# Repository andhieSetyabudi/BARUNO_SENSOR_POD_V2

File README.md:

# BARUNO_SENSOR_POD_V2https://github.com/andhieSetyabudi/BARUNO_SENSOR_POD_V2
Baruno sensor pod revision

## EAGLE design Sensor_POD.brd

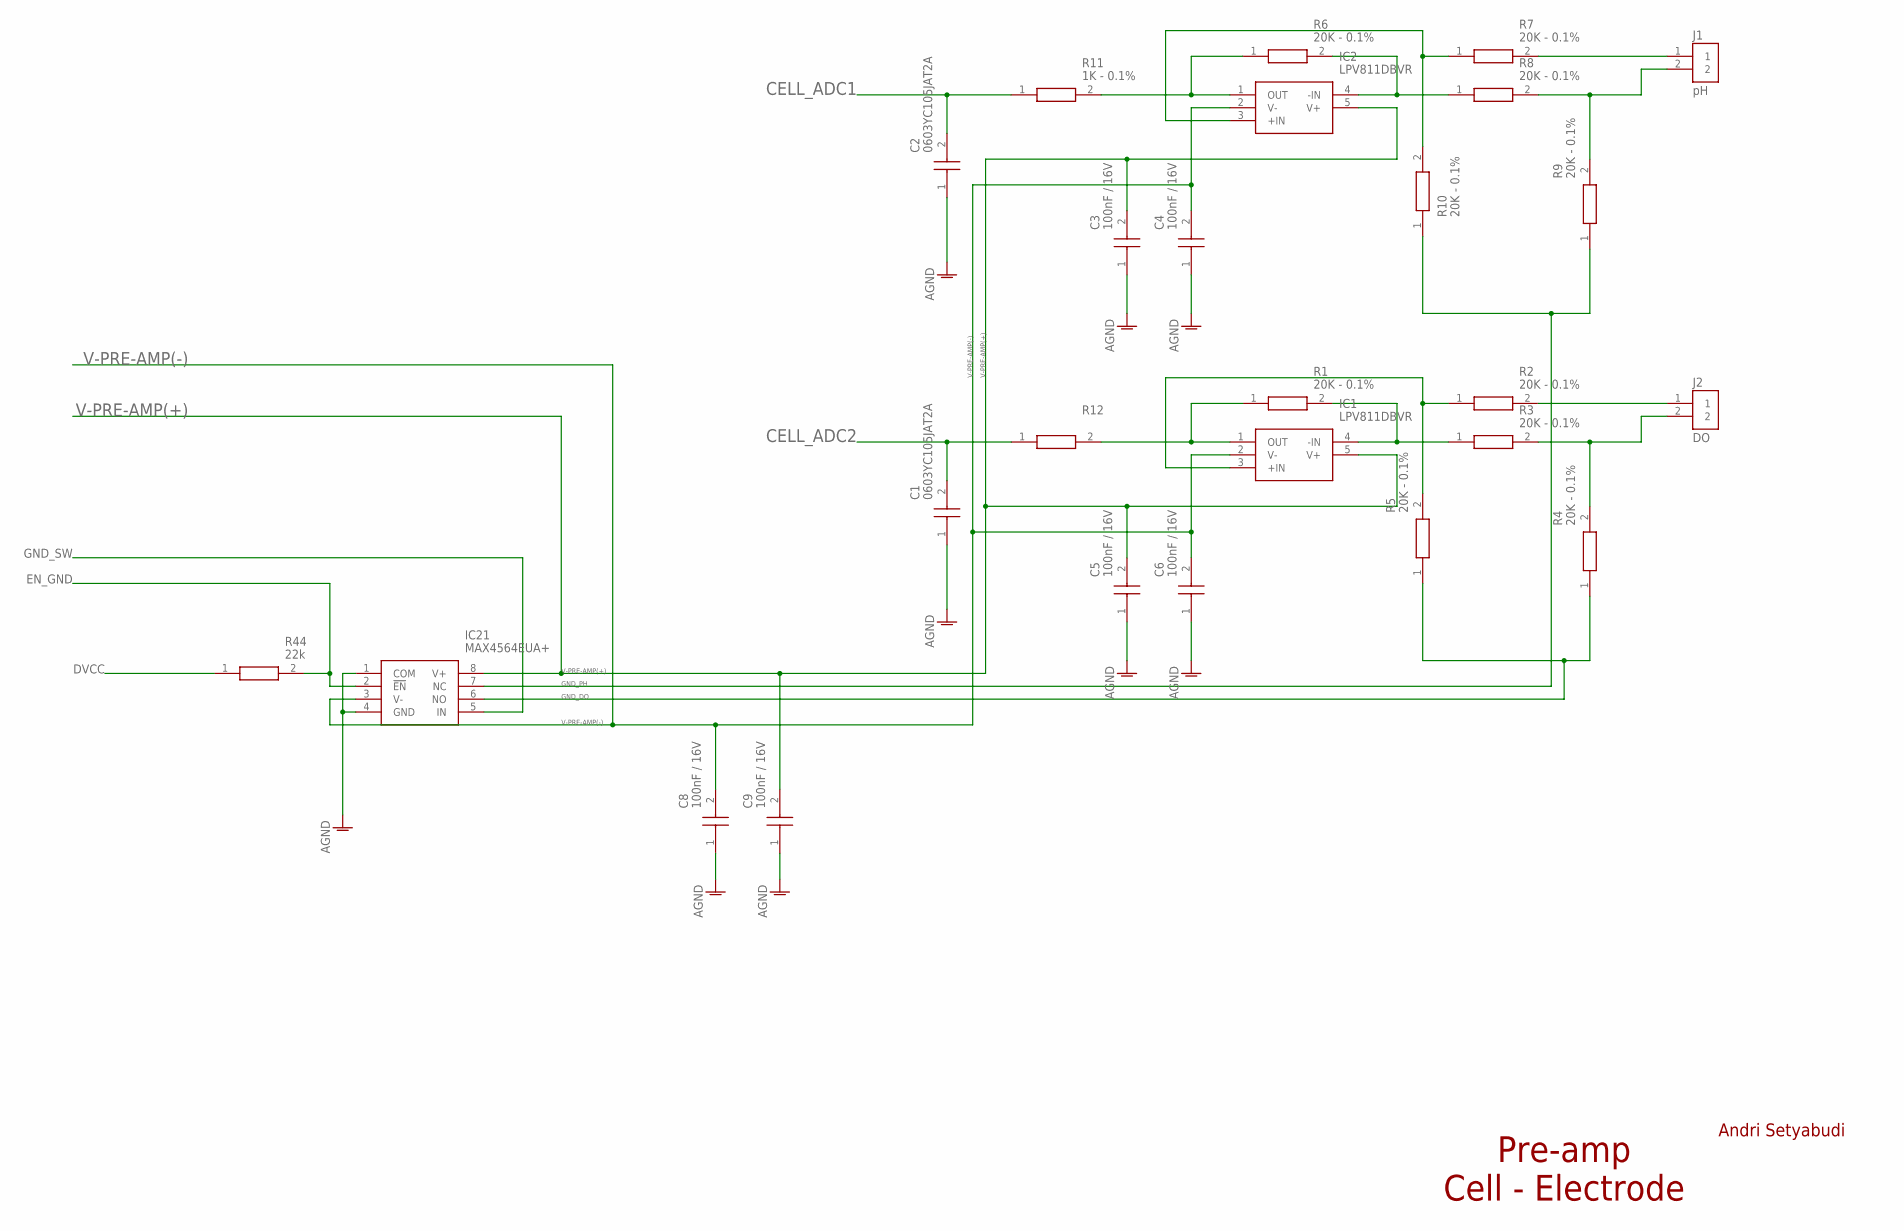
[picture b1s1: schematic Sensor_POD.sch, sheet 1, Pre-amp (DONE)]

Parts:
C1, C2: 0603YC105JAT2A; CAPC1608X90N
C3, C4, C5, C6, C8, C9: 100nF / 16V; CAPC1608X90N
IC1, IC2: LPV811DBVR; SOT95P280X145-5N
IC21: MAX4564EUA+; SOP65P490X110-8N
J1: pH; JST_B2B-PH-K-S(LF)(SN)
J2: DO; JST_B2B-PH-K-S(LF)(SN)
R1, R2, R3, R4, R5, R6, R7, R8, R9, R10: 20K - 0.1%; RESC1608X55N@2
R11: 1K - 0.1%; RESC1608X50N
R12: RG1608P-102-B-T5; RESC1608X50N
R44: 22k; RESC1608X55N

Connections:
AGND: C1.1, C2.1, C3.1, C4.1, C5.1, C6.1, C8.1, C9.1, IC21.1 (COM), IC21.4 (GND); also elsewhere on the board
CELL_ADC1: C2.2, R11.1; also elsewhere on the board
CELL_ADC2: C1.2, R12.1; also elsewhere on the board
DVCC: R44.1; also elsewhere on the board
EN_GND: IC21.2 (!EN), R44.2; also elsewhere on the board
GND_DO: IC21.6 (NO), R4.1, R5.1
GND_PH: IC21.7 (NC), R9.1, R10.1
GND_SW: IC21.5 (IN); also elsewhere on the board
unnamed: IC1.4 (-IN), R1.2, R3.1
unnamed: IC1.1 (OUT), R1.1, R12.2
unnamed: IC1.3 (+IN), R2.1, R5.2
unnamed: J2.2, R3.2, R4.2
unnamed: J2.1, R2.2
unnamed: IC2.4 (-IN), R6.2, R8.1
unnamed: IC2.1 (OUT), R6.1, R11.2
unnamed: IC2.3 (+IN), R7.1, R10.2
unnamed: J1.2, R8.2, R9.2
unnamed: J1.1, R7.2
V-PRE-AMP(+): C3.2, C5.2, C9.2, IC1.5 (V+), IC2.5 (V+), IC21.8 (V+); also elsewhere on the board
V-PRE-AMP(-): C4.2, C6.2, C8.2, IC1.2 (V-), IC2.2 (V-), IC21.3 (V-); also elsewhere on the board

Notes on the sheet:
Andri Setyabudi
Pre-amp Cell - Electrode

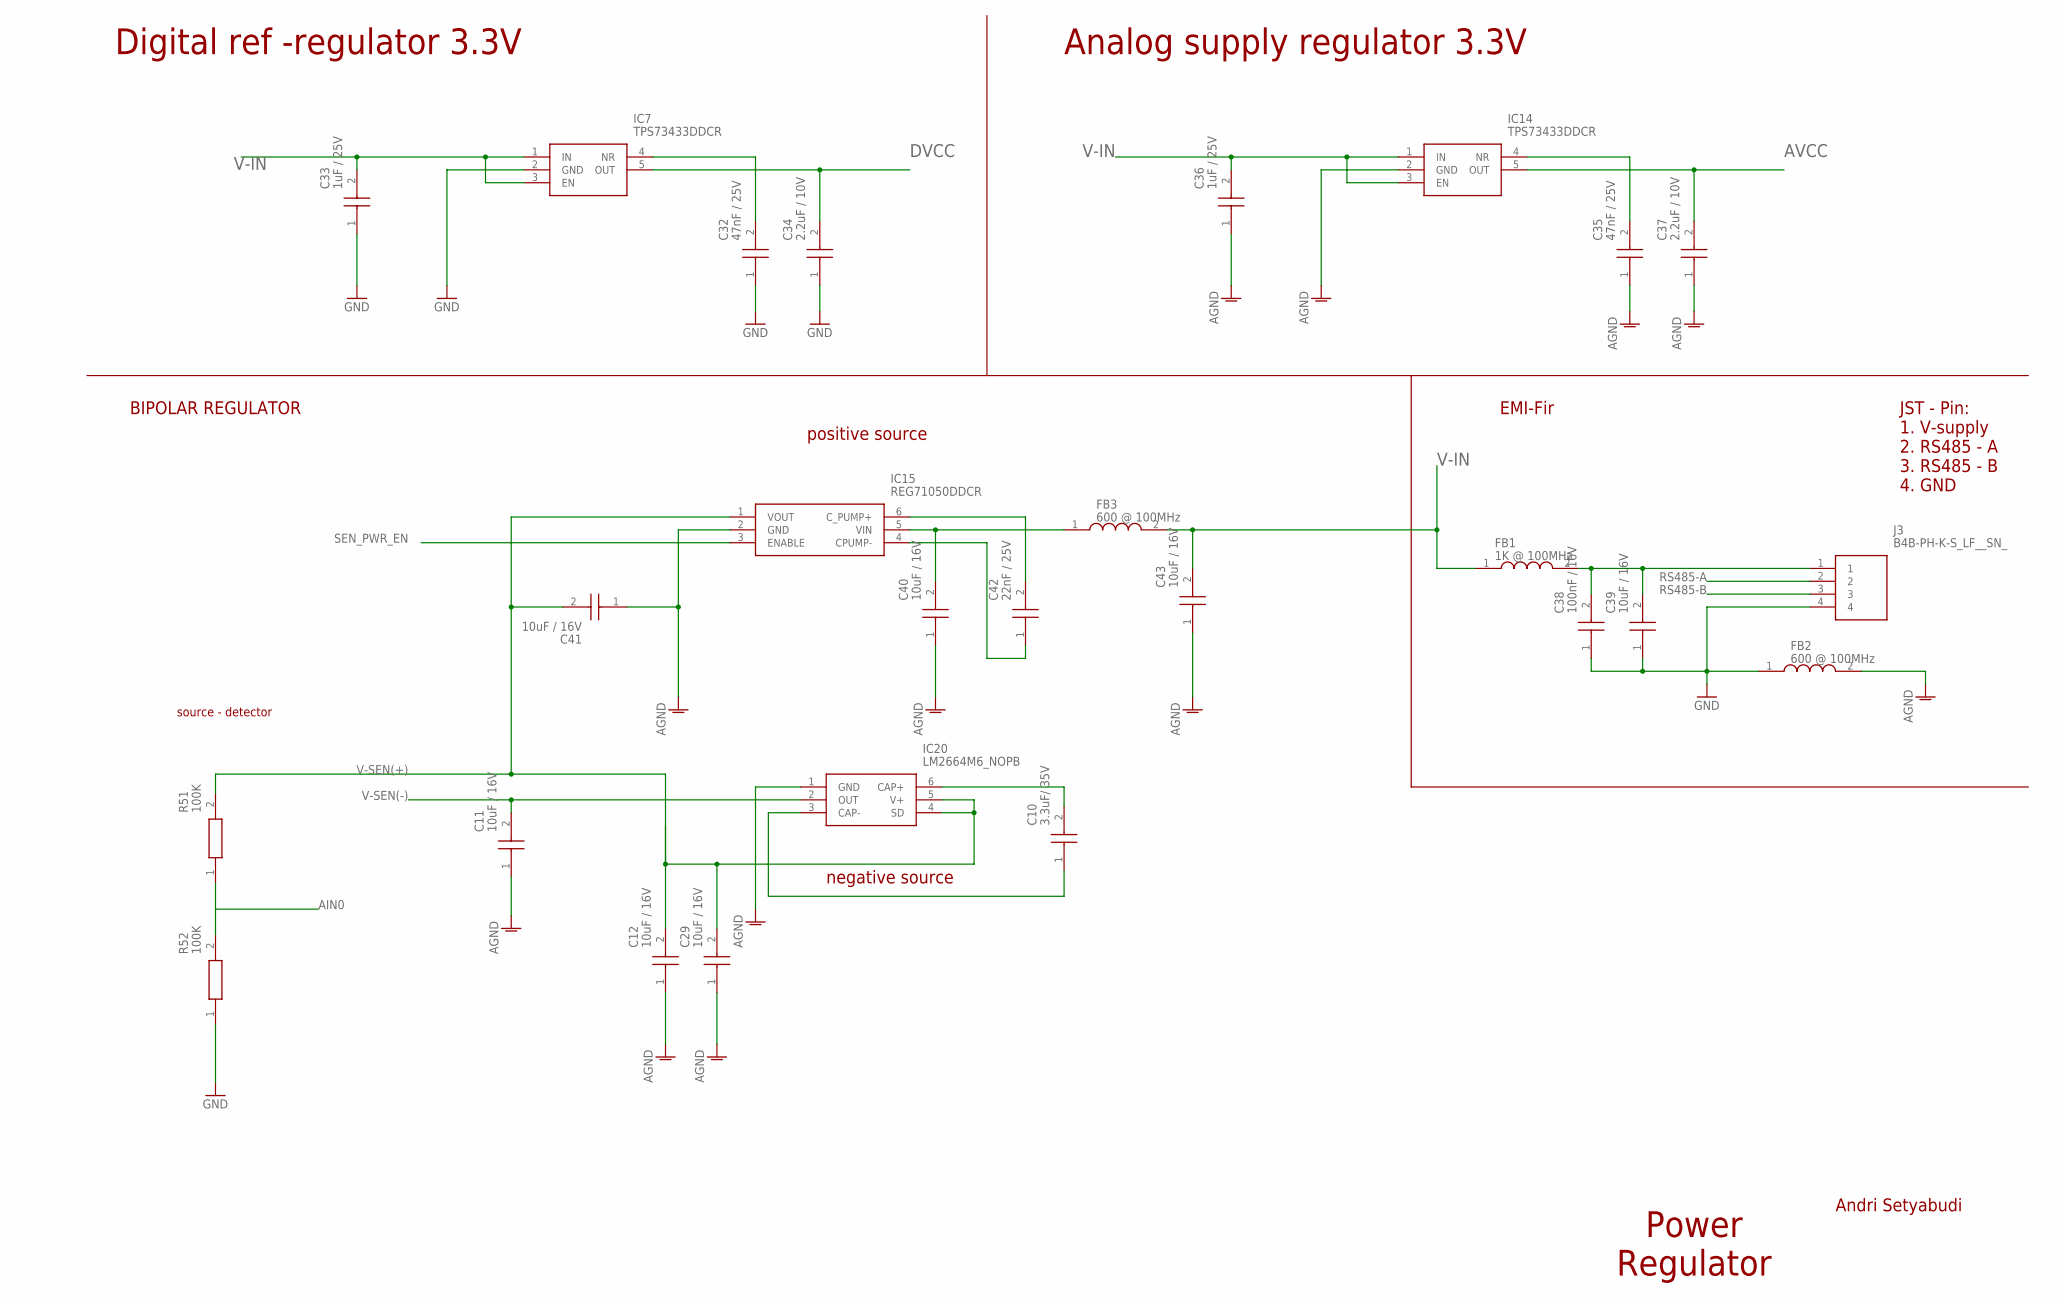
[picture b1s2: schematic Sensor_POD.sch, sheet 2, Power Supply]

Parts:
C10: 3.3uF/ 35V; CAPC1608X90N
C11, C12, C29, C39, C40, C41, C43: 10uF / 16V; CAPC1608X100N
C32, C35: 47nF / 25V; CAPC1608X90N@1
C33, C36: 1uF / 25V; CAPC1608X90N@1
C34, C37: 2.2uF / 10V; CAPC1608X90N@1
C38: 100nF / 16V; CAPC1608X90N@1
C42: 22nF / 25V; CAPC1608X90N@1
FB1: 1K @ 100MHz; BLM18KG102SH1J
FB2, FB3: 600 @ 100MHz; BEADC1608X75N
IC7, IC14: TPS73433DDCR; SOT95P280X110-5N
IC15: REG71050DDCR; SOT95P280X110-6N
IC20: LM2664M6_NOPB; SOT95P280X145-6N
J3: B4B-PH-K-S_LF__SN_; SHDR4W50P0X200_1X4_990X450X600
R51, R52: 100K; RESC1608X55N@1

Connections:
AGND: C11.1, C12.1, C29.1, C35.1, C36.1, C37.1, C40.1, C41.1, C43.1, FB2.2, IC14.2 (GND), IC15.2 (GND), IC20.1 (GND); also elsewhere on the board
AIN0: R51.1, R52.2; also elsewhere on the board
AVCC: C37.2, IC14.5 (OUT); also elsewhere on the board
DVCC: C34.2, IC7.5 (OUT); also elsewhere on the board
GND: C32.1, C33.1, C34.1, C38.1, C39.1, FB2.1, IC7.2 (GND), J3.4, R52.1; also elsewhere on the board
unnamed: C42.2, IC15.6 (C_PUMP+)
unnamed: C10.2, IC20.6 (CAP+)
unnamed: C42.1, IC15.4 (CPUMP-)
unnamed: C10.1, IC20.3 (CAP-)
unnamed: C32.2, IC7.4 (NR)
unnamed: C40.2, FB3.1, IC15.5 (VIN)
unnamed: C35.2, IC14.4 (NR)
unnamed: C38.2, C39.2, FB1.2, J3.1
RS485-A: J3.2; also elsewhere on the board
RS485-B: J3.3; also elsewhere on the board
SEN_PWR_EN: IC15.3 (ENABLE); also elsewhere on the board
V-IN: C33.2, C36.2, C43.2, FB1.1, FB3.2, IC7.1 (IN), IC7.3 (EN), IC14.1 (IN), IC14.3 (EN); also elsewhere on the board
V-SEN(+): C12.2, C29.2, C41.2, IC15.1 (VOUT), IC20.4 (SD), IC20.5 (V+), R51.2; also elsewhere on the board
V-SEN(-): C11.2, IC20.2 (OUT); also elsewhere on the board

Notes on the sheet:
Andri Setyabudi
Power Regulator
negative source
Digital ref -regulator 3.3V
Analog supply regulator 3.3V
BIPOLAR REGULATOR
EMI-Fir
JST - Pin: 1. V-supply 2. RS485 - A 3. RS485 - B 4. GND
positive source
source - detector

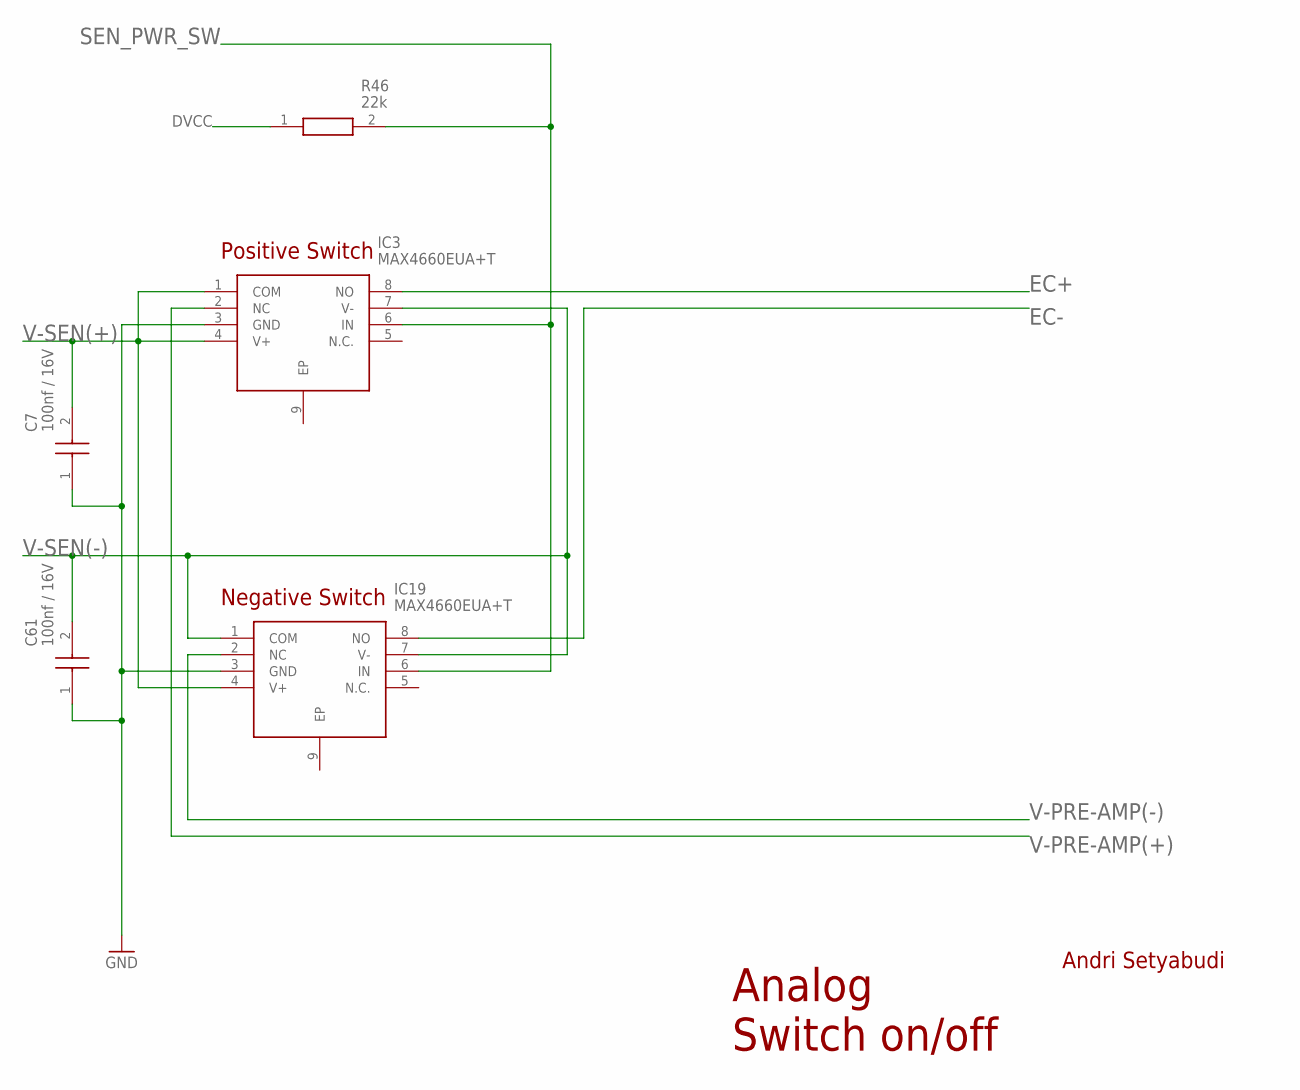
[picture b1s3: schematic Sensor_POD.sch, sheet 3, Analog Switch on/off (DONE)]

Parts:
C7, C61: 100nf / 16V; CAPC1608X90N
IC3, IC19: MAX4660EUA+T; SOP65P490X110-9N
R46: 22k; RESC1608X55N

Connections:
DVCC: R46.1; also elsewhere on the board
EC+: IC3.8 (NO); also elsewhere on the board
EC-: IC19.8 (NO); also elsewhere on the board
GND: C7.1, C61.1, IC3.3 (GND), IC19.3 (GND); also elsewhere on the board
SEN_PWR_SW: IC3.6 (IN), IC19.6 (IN), R46.2
V-PRE-AMP(+): IC3.2 (NC); also elsewhere on the board
V-PRE-AMP(-): IC19.2 (NC); also elsewhere on the board
V-SEN(+): C7.2, IC3.1 (COM), IC3.4 (V+), IC19.4 (V+); also elsewhere on the board
V-SEN(-): C61.2, IC3.7 (V-), IC19.1 (COM), IC19.7 (V-); also elsewhere on the board

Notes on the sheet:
Andri Setyabudi
Analog Switch on/off
Positive Switch
Negative Switch

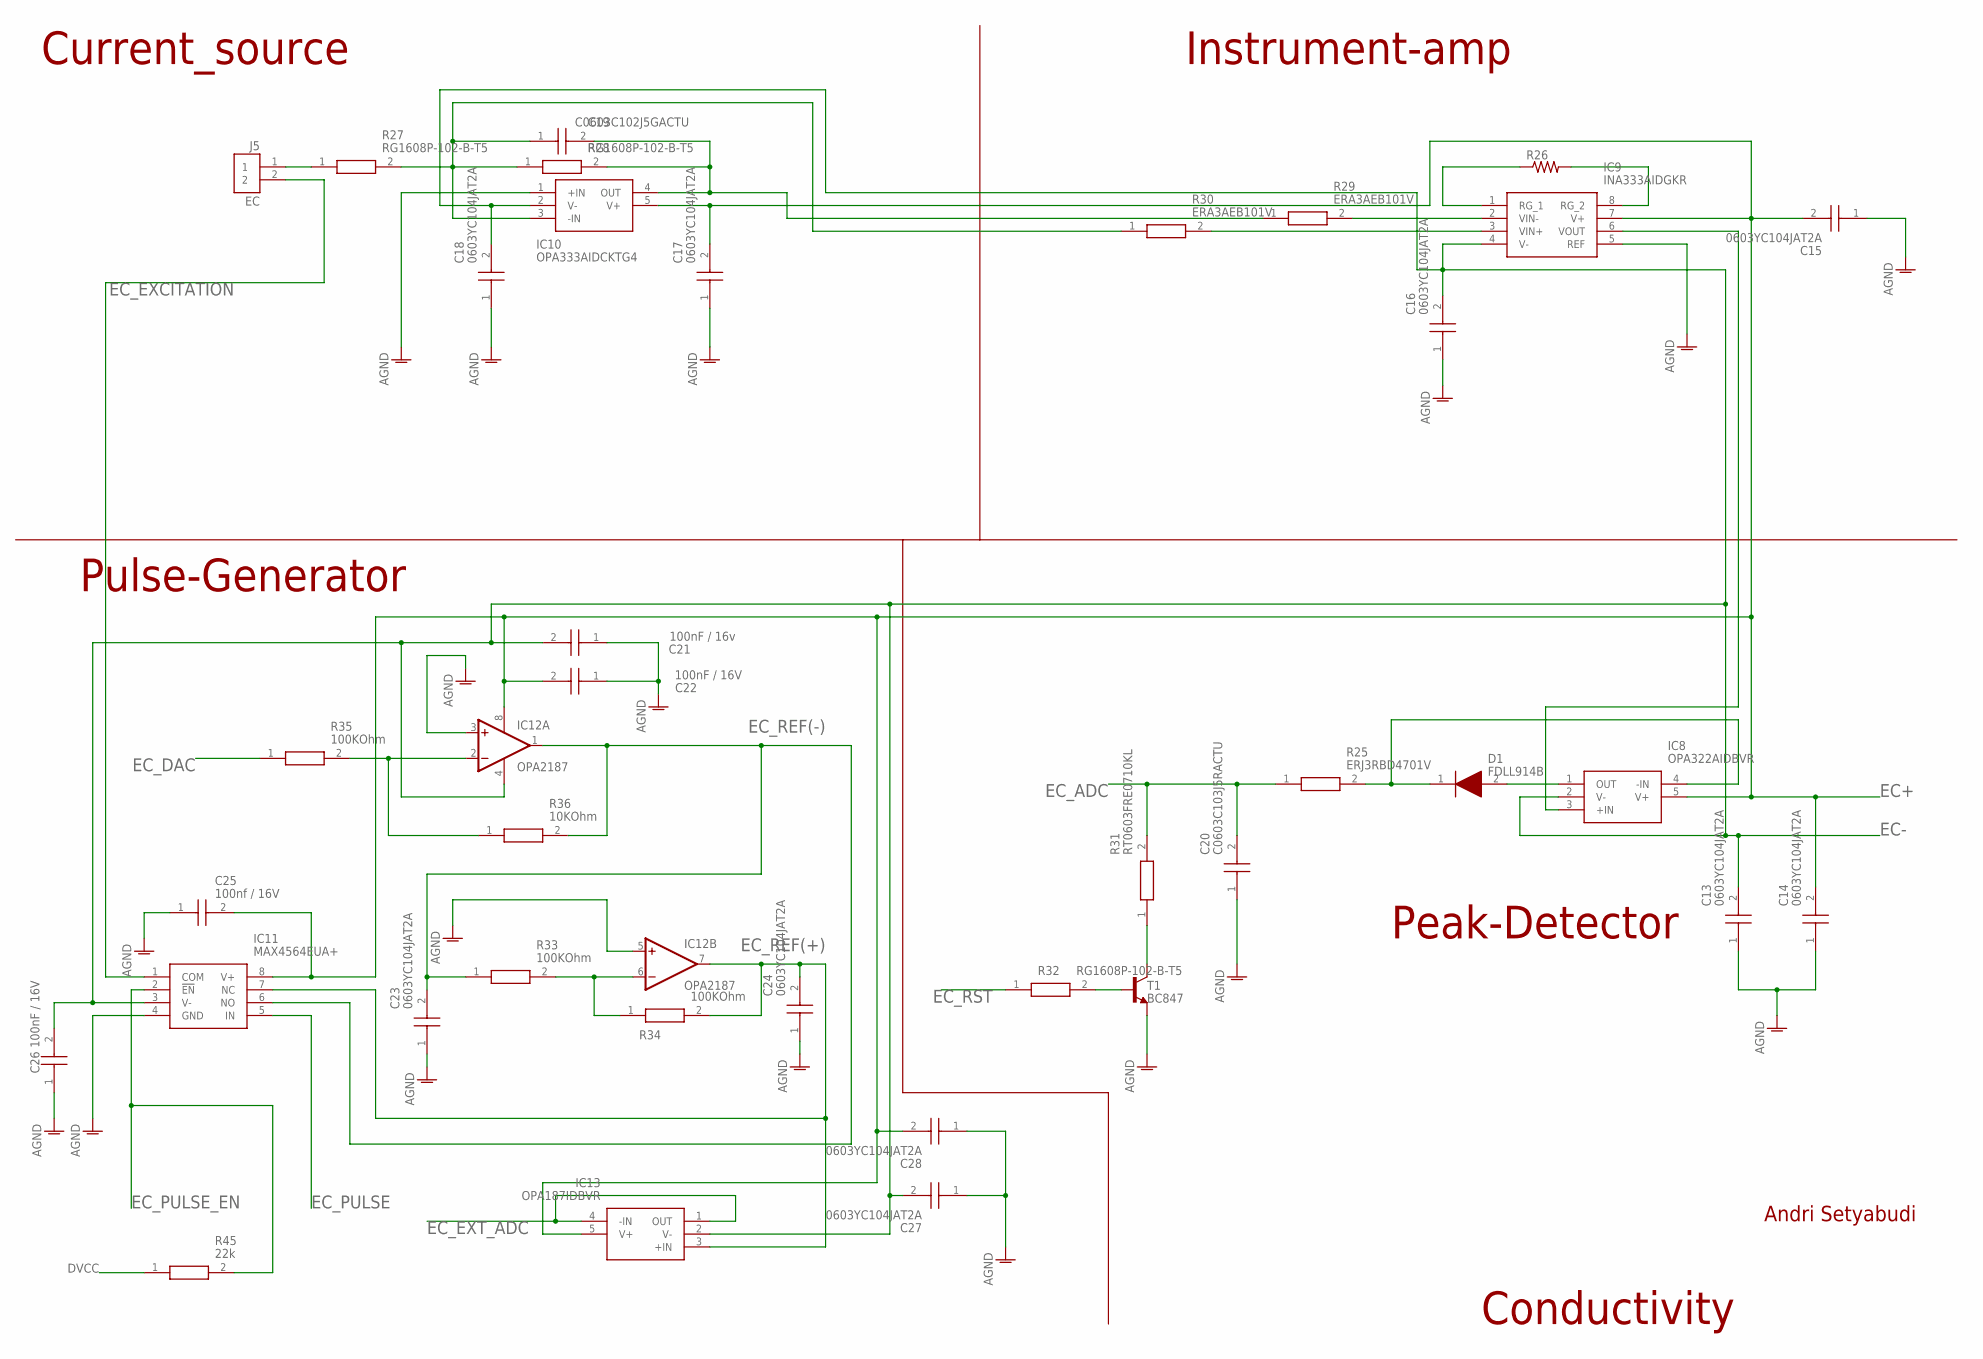
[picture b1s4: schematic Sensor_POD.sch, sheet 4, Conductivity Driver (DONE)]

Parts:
C13, C14, C15, C16, C17, C18, C23, C24, C27, C28: 0603YC104JAT2A; CAPC1608X90N
C19: C0603C102J5GACTU; CAPC1608X85N
C20: C0603C103J5RACTU; CAPC1608X87N
C21: 100nF / 16v; CAPC1608X90N
C22, C26: 100nF / 16V; CAPC1608X90N
C25: 100nf / 16V; CAPC1608X90N
D1: FDLL914B
IC8: OPA322AIDBVR; SOT95P280X145-5N
IC9: INA333AIDGKR; SOP65P490X110-8N
IC10: OPA333AIDCKTG4; SOT65P210X110-5N
IC11: MAX4564EUA+; SOP65P490X110-8N
IC12: OPA2187; SO08
IC13: OPA187IDBVR; SOT95P280X145-5N
J5: EC; JST_B2B-PH-K-S(LF)(SN)
R25: ERJ3RBD4701V; RESC1608X55N
R26: R-US_R0603; R0603
R27, R28, R32: RG1608P-102-B-T5; RESC1608X50N
R29, R30: ERA3AEB101V; RESC1608X55N@2
R31: RT0603FRE0710KL; RESC1608X55N@2
R33, R34, R35: 100KOhm; RESC1608X55N@1
R36: 10KOhm; RESC1608X55N@2
R45: 22k; RESC1608X55N
T1: BC847; SOT23

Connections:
AGND: C13.1, C14.1, C15.1, C16.1, C17.1, C18.1, C20.1, C21.1, C22.1, C23.1, C24.1, C25.1, C26.1, C27.1, C28.1, IC9.5 (REF), IC10.1 (+IN), IC11.4 (GND), IC12.3 (+IN), IC12.5 (+IN), T1.2 (E); also elsewhere on the board
DVCC: R45.1; also elsewhere on the board
EC+: C14.2, C15.2, C17.2, C22.2, C25.2, C28.2, IC8.5 (V+), IC9.7 (V+), IC10.5 (V+), IC11.8 (V+), IC12.8 (V+), IC13.5 (V+); also elsewhere on the board
EC-: C13.2, C16.2, C18.2, C21.2, C26.2, C27.2, IC8.2 (V-), IC9.4 (V-), IC10.2 (V-), IC11.3 (V-), IC12.4 (V-), IC13.2 (V-); also elsewhere on the board
EC_ADC: C20.2, R25.1, R31.2; also elsewhere on the board
EC_DAC: R35.1; also elsewhere on the board
EC_EXCITATION: IC11.1 (COM), J5.2
EC_EXT_ADC: IC13.1 (OUT), IC13.4 (-IN); also elsewhere on the board
EC_PULSE: IC11.5 (IN); also elsewhere on the board
EC_PULSE_EN: IC11.2 (!EN), R45.2; also elsewhere on the board
EC_REF(+): C24.2, IC11.7 (NC), IC12.7 (OUT), IC13.3 (+IN), R34.2
EC_REF(-): C23.2, IC11.6 (NO), IC12.1 (OUT), R33.1, R36.2
EC_RST: R32.1; also elsewhere on the board
unnamed: D1.2 (A), IC8.1 (OUT)
unnamed: D1.1 (K), IC8.4 (-IN), R25.2
unnamed: R31.1, T1.3 (C)
unnamed: R32.2, T1.1 (B)
unnamed: IC9.8 (RG_2), R26.2
unnamed: IC9.1 (RG_1), R26.1
unnamed: J5.1, R27.1
unnamed: IC12.6 (-IN), R33.2, R34.1
unnamed: C19.1 (C1), IC10.3 (-IN), R27.2, R28.1, R30.1
unnamed: C19.2 (C2), IC10.4 (OUT), R28.2, R29.1
unnamed: IC9.2 (VIN-), R29.2
unnamed: IC9.3 (VIN+), R30.2
unnamed: IC12.2 (-IN), R35.2, R36.1
unnamed: IC8.3 (+IN), IC9.6 (VOUT)

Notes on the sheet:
Andri Setyabudi
Conductivity
Current_source
Instrument-amp
Peak-Detector
Pulse-Generator

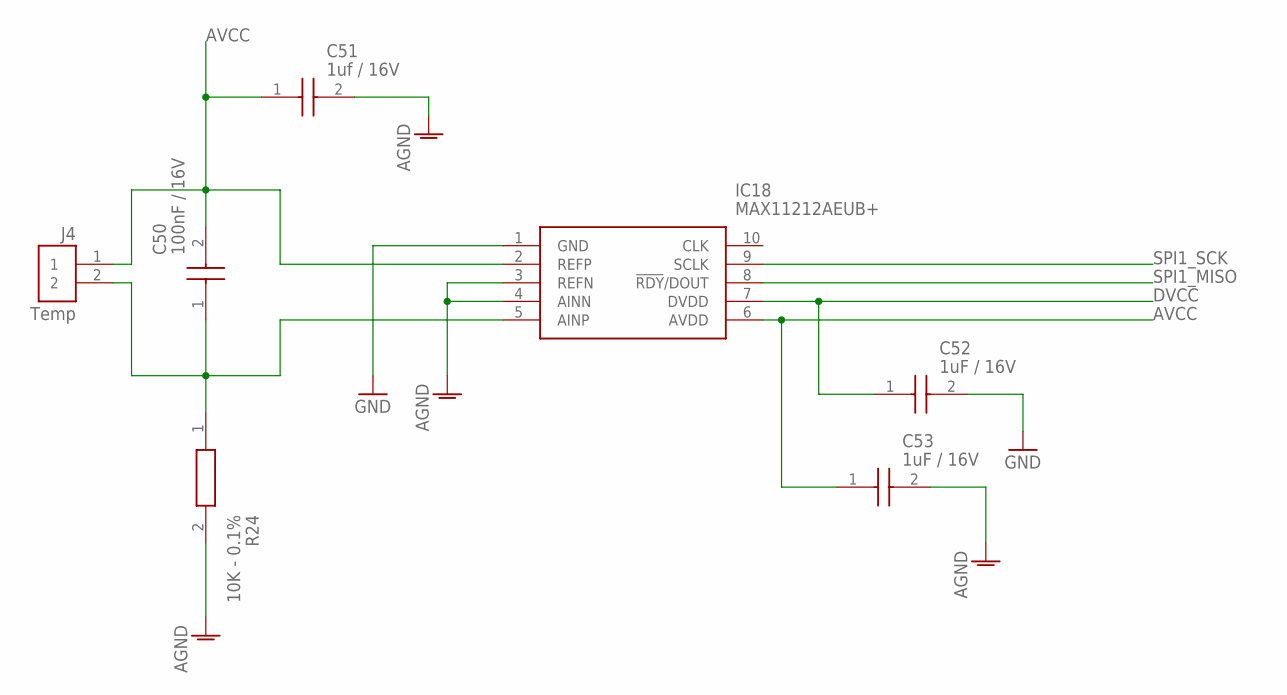
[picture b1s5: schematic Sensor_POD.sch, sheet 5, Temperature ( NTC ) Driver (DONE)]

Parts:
C50: 100nF / 16V; CAPC1608X90N
C51: 1uf / 16V; CAPC1608X90N
C52, C53: 1uF / 16V; CAPC1608X90N
IC18: MAX11212AEUB+; SOP50P490X110-10N
J4: Temp; JST_B2B-PH-K-S(LF)(SN)
R24: 10K - 0.1%; RESC1608X55N@2

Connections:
AGND: C51.2, C53.2, IC18.3 (REFN), IC18.4 (AINN), R24.2; also elsewhere on the board
AVCC: C50.2, C51.1, C53.1, IC18.2 (REFP), IC18.6 (AVDD), J4.1; also elsewhere on the board
DVCC: C52.1, IC18.7 (DVDD); also elsewhere on the board
GND: C52.2, IC18.1 (GND); also elsewhere on the board
unnamed: C50.1, IC18.5 (AINP), J4.2, R24.1
SPI1_MISO: IC18.8 (!RDY!/DOUT); also elsewhere on the board
SPI1_SCK: IC18.9 (SCLK); also elsewhere on the board

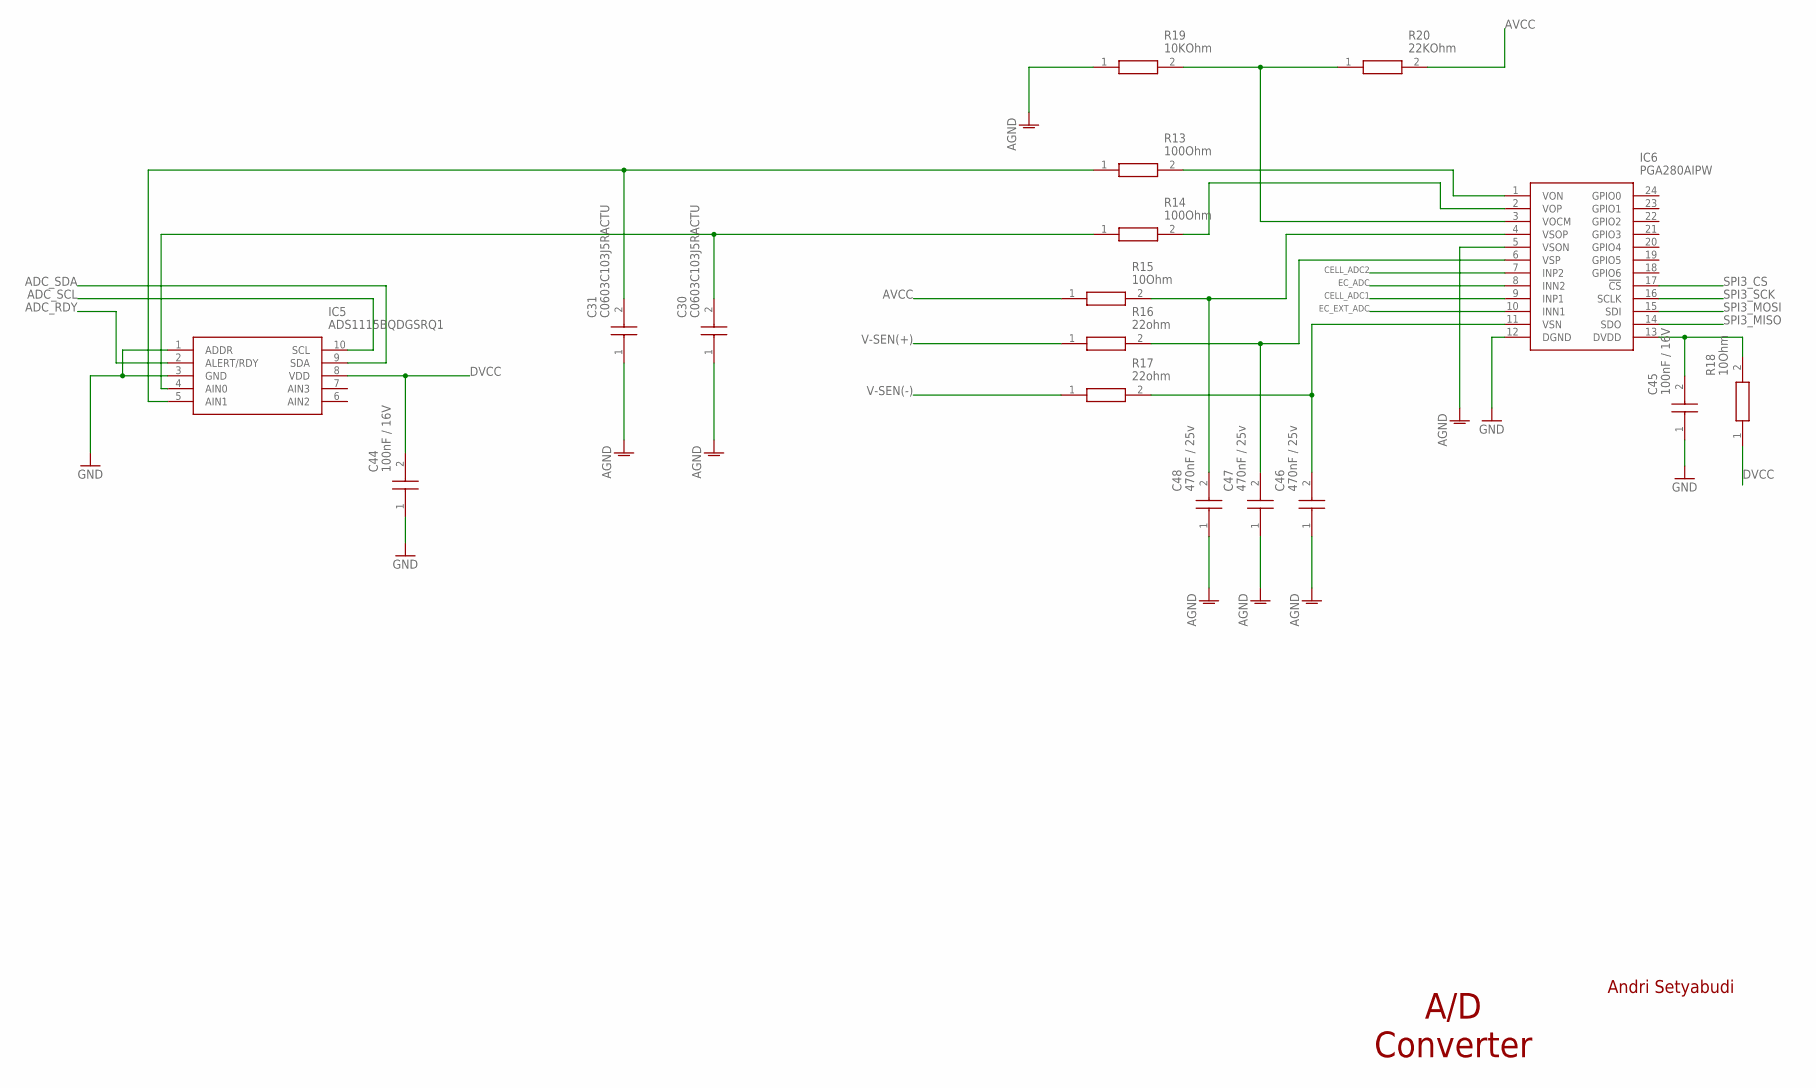
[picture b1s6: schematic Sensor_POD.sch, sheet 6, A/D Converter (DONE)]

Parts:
C30, C31: C0603C103J5RACTU; CAPC1608X87N
C44, C45: 100nF / 16V; CAPC1608X90N
C46, C47, C48: 470nF / 25v; CAPC1608X90N@1
IC5: ADS1115BQDGSRQ1; SOP50P490X110-10N
IC6: PGA280AIPW; SOP65P640X120-24N
R13, R14: 100Ohm; RESC1608X55N@2
R15, R18: 10Ohm; RESC1608X55N@2
R16, R17: 22ohm; RESC1608X55N@2
R19: 10KOhm; RESC1608X55N@2
R20: 22KOhm; RESC1608X55N

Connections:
ADC_RDY: IC5.2 (ALERT/RDY); also elsewhere on the board
ADC_SCL: IC5.10 (SCL); also elsewhere on the board
ADC_SDA: IC5.9 (SDA); also elsewhere on the board
AGND: C30.1, C31.1, C46.1, C47.1, C48.1, IC6.5 (VSON), R19.1; also elsewhere on the board
AVCC: R15.1, R20.2; also elsewhere on the board
CELL_ADC1: IC6.9 (INP1); also elsewhere on the board
CELL_ADC2: IC6.7 (INP2); also elsewhere on the board
DVCC: C44.2, IC5.8 (VDD), R18.1; also elsewhere on the board
EC_ADC: IC6.8 (INN2); also elsewhere on the board
EC_EXT_ADC: IC6.10 (INN1); also elsewhere on the board
GND: C44.1, C45.1, IC5.1 (ADDR), IC5.3 (GND), IC6.12 (DGND); also elsewhere on the board
unnamed: C30.2, IC5.4 (AIN0), R14.1
unnamed: C31.2, IC5.5 (AIN1), R13.1
unnamed: IC6.1 (VON), R13.2
unnamed: IC6.3 (VOCM), R19.2, R20.1
unnamed: IC6.2 (VOP), R14.2
unnamed: C48.2, IC6.4 (VSOP), R15.2
unnamed: C47.2, IC6.6 (VSP), R16.2
unnamed: C46.2, IC6.11 (VSN), R17.2
unnamed: C45.2, IC6.13 (DVDD), R18.2
SPI3_CS: IC6.17 (!CS); also elsewhere on the board
SPI3_MISO: IC6.14 (SDO); also elsewhere on the board
SPI3_MOSI: IC6.15 (SDI); also elsewhere on the board
SPI3_SCK: IC6.16 (SCLK); also elsewhere on the board
V-SEN(+): R16.1; also elsewhere on the board
V-SEN(-): R17.1; also elsewhere on the board

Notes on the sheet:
Andri Setyabudi
A/D Converter

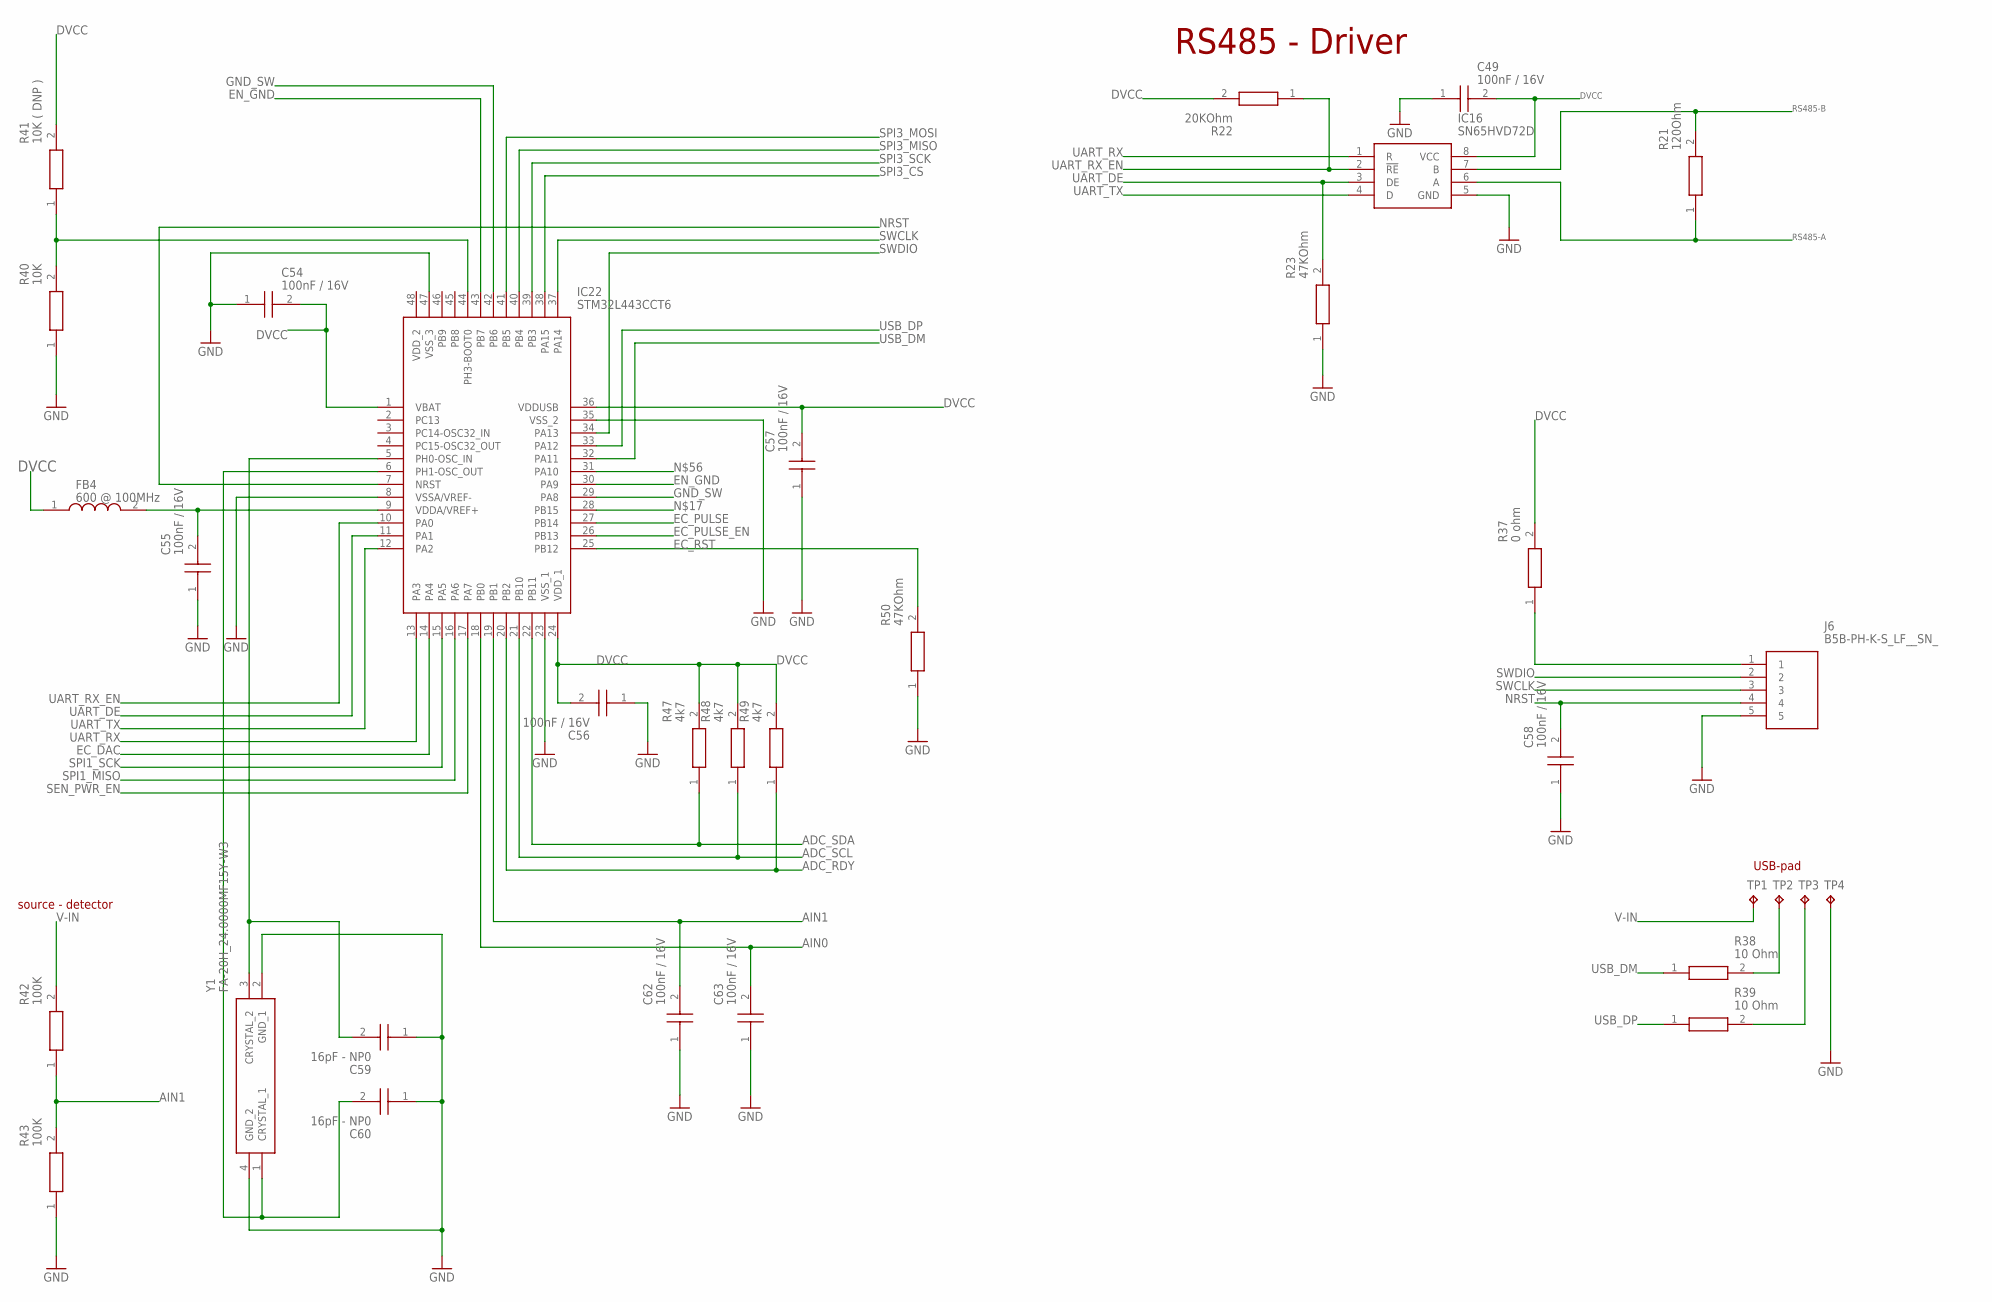
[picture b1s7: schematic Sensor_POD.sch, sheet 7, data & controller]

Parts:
C49: 100nF / 16V; CAPC1608X90N
C54, C55, C56, C57, C58, C62, C63: 100nF / 16V; CAPC1608X90N@1
C59, C60: 16pF - NP0; CAPC1608X97N
FB4: 600 @ 100MHz; BEADC1608X75N
IC16: SN65HVD72D; SOIC127P600X175-8N
IC22: STM32L443CCT6; QFP50P900X900X160-48N
J6: B5B-PH-K-S_LF__SN_; SHDR5W50P0X200_1X5_1190X450X60
R21: 120Ohm; RESC1608X55N@2
R22: 20KOhm; RESC1608X55N@2
R23, R50: 47KOhm; RESC1608X55N@2
R37: 0 ohm; RESC1608X55N@2
R38, R39: 10 Ohm; RESC1608X55N@2
R40: 10K; RESC1608X55N@2
R41: 10K ( DNP ); RESC1608X55N@2
R42, R43: 100K; RESC1608X55N@1
R47, R48, R49: 4k7; RESC1608X55N
TP1, TP2, TP3, TP4: TPB1,27; B1,27
Y1: FA-20H_24.0000MF15Y-W3; FA20H160000MF12ZAC3

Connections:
ADC_RDY: IC22.20 (PB2), R49.1; also elsewhere on the board
ADC_SCL: IC22.21 (PB10), R48.1; also elsewhere on the board
ADC_SDA: IC22.22 (PB11), R47.1; also elsewhere on the board
AIN0: C63.2, IC22.18 (PB0); also elsewhere on the board
AIN1: C62.2, IC22.19 (PB1), R42.1, R43.2
DVCC: C49.2, C54.2, C56.2, C57.2, FB4.1, IC16.8 (VCC), IC22.1 (VBAT), IC22.24 (VDD_1), IC22.36 (VDDUSB), R22.2, R37.2, R41.2, R47.2, R48.2, R49.2; also elsewhere on the board
EC_DAC: IC22.14 (PA4); also elsewhere on the board
EC_PULSE: IC22.27 (PB14); also elsewhere on the board
EC_PULSE_EN: IC22.26 (PB13); also elsewhere on the board
EC_RST: IC22.25 (PB12), R50.2; also elsewhere on the board
EN_GND: IC22.30 (PA9), IC22.43 (PB7); also elsewhere on the board
GND: C49.1, C54.1, C55.1, C56.1, C57.1, C58.1, C59.1, C60.1, C62.1, C63.1, IC16.5 (GND), IC22.8 (VSSA/VREF-), IC22.23 (VSS_1), IC22.35 (VSS_2), IC22.47 (VSS_3), J6.5, R23.1, R40.1, R43.1, R50.1, TP4.TP, Y1.2 (GND_1), Y1.4 (GND_2); also elsewhere on the board
GND_SW: IC22.29 (PA8), IC22.42 (PB6); also elsewhere on the board
unnamed: IC22.44 (PH3-BOOT0), R40.2, R41.1
unnamed: J6.1, R37.1
unnamed: R38.2, TP2.TP
unnamed: R39.2, TP3.TP
unnamed: C60.2, IC22.6 (PH1-OSC_OUT), Y1.1 (CRYSTAL_1)
unnamed: C59.2, IC22.5 (PH0-OSC_IN), Y1.3 (CRYSTAL_2)
unnamed: C55.2, FB4.2, IC22.9 (VDDA/VREF+)
NRST: C58.2, IC22.7 (NRST), J6.4
RS485-A: IC16.6 (A), R21.1; also elsewhere on the board
RS485-B: IC16.7 (B), R21.2; also elsewhere on the board
SEN_PWR_EN: IC22.17 (PA7); also elsewhere on the board
SPI1_MISO: IC22.16 (PA6); also elsewhere on the board
SPI1_SCK: IC22.15 (PA5); also elsewhere on the board
SPI3_CS: IC22.38 (PA15); also elsewhere on the board
SPI3_MISO: IC22.40 (PB4); also elsewhere on the board
SPI3_MOSI: IC22.41 (PB5); also elsewhere on the board
SPI3_SCK: IC22.39 (PB3); also elsewhere on the board
SWCLK: IC22.37 (PA14), J6.3
SWDIO: IC22.34 (PA13), J6.2
UART_DE: IC16.3 (DE), IC22.11 (PA1), R23.2
UART_RX: IC16.1 (R), IC22.13 (PA3)
UART_RX_EN: IC16.2 (!RE), IC22.10 (PA0), R22.1
UART_TX: IC16.4 (D), IC22.12 (PA2)
USB_DM: IC22.32 (PA11), R38.1
USB_DP: IC22.33 (PA12), R39.1
V-IN: R42.2, TP1.TP; also elsewhere on the board

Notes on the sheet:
RS485 - Driver
USB-pad
source - detector

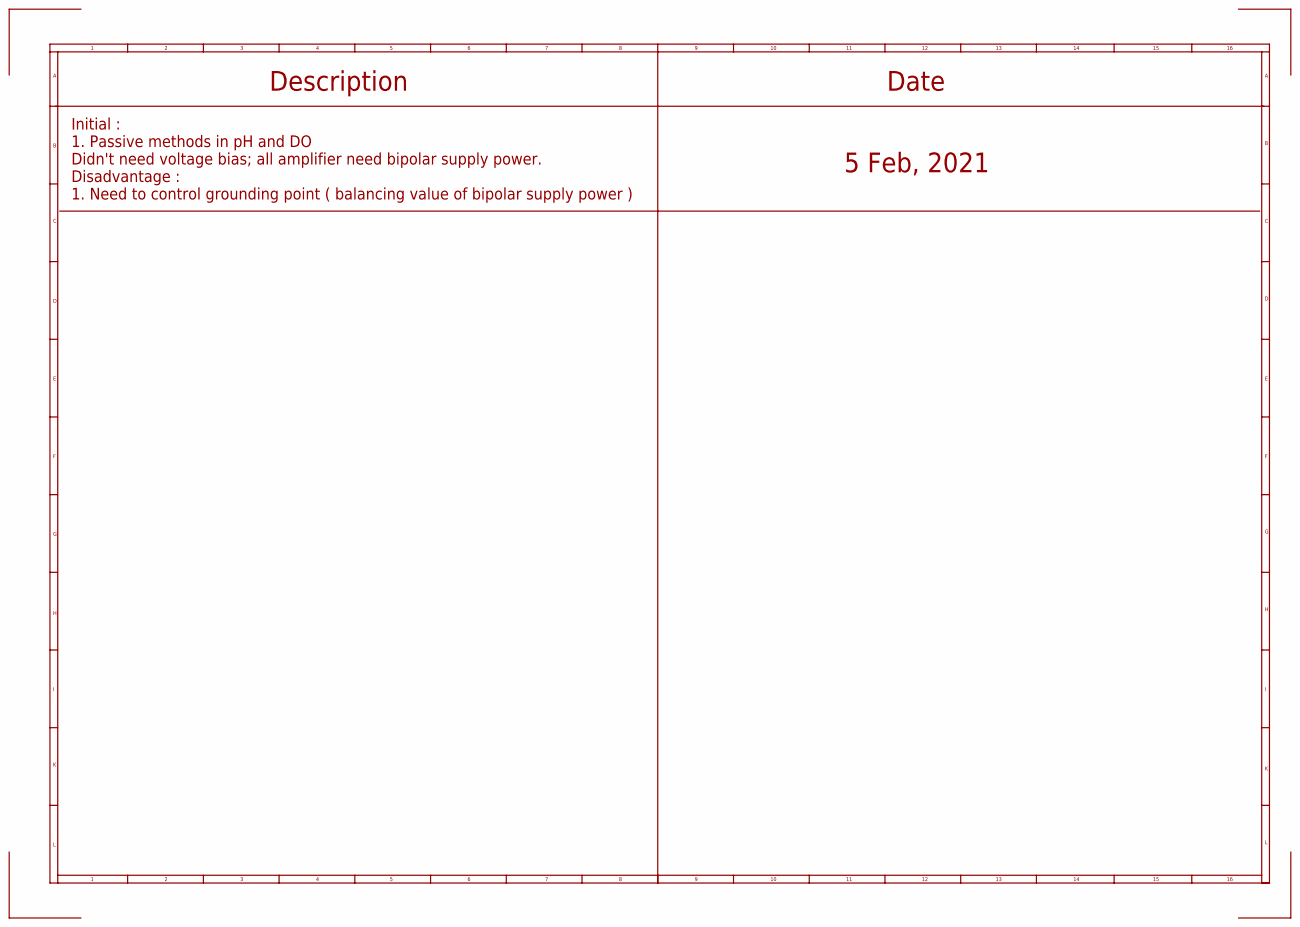
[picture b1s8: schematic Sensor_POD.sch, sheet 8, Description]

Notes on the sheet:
Description
Date
Initial : 1. Passive methods in pH and DO Didn't need voltage bias; all amplifier need bipolar supply power. Disadvantage : 1. Need to control grounding point ( balancing value of bipolar supply power )
5 Feb, 2021
